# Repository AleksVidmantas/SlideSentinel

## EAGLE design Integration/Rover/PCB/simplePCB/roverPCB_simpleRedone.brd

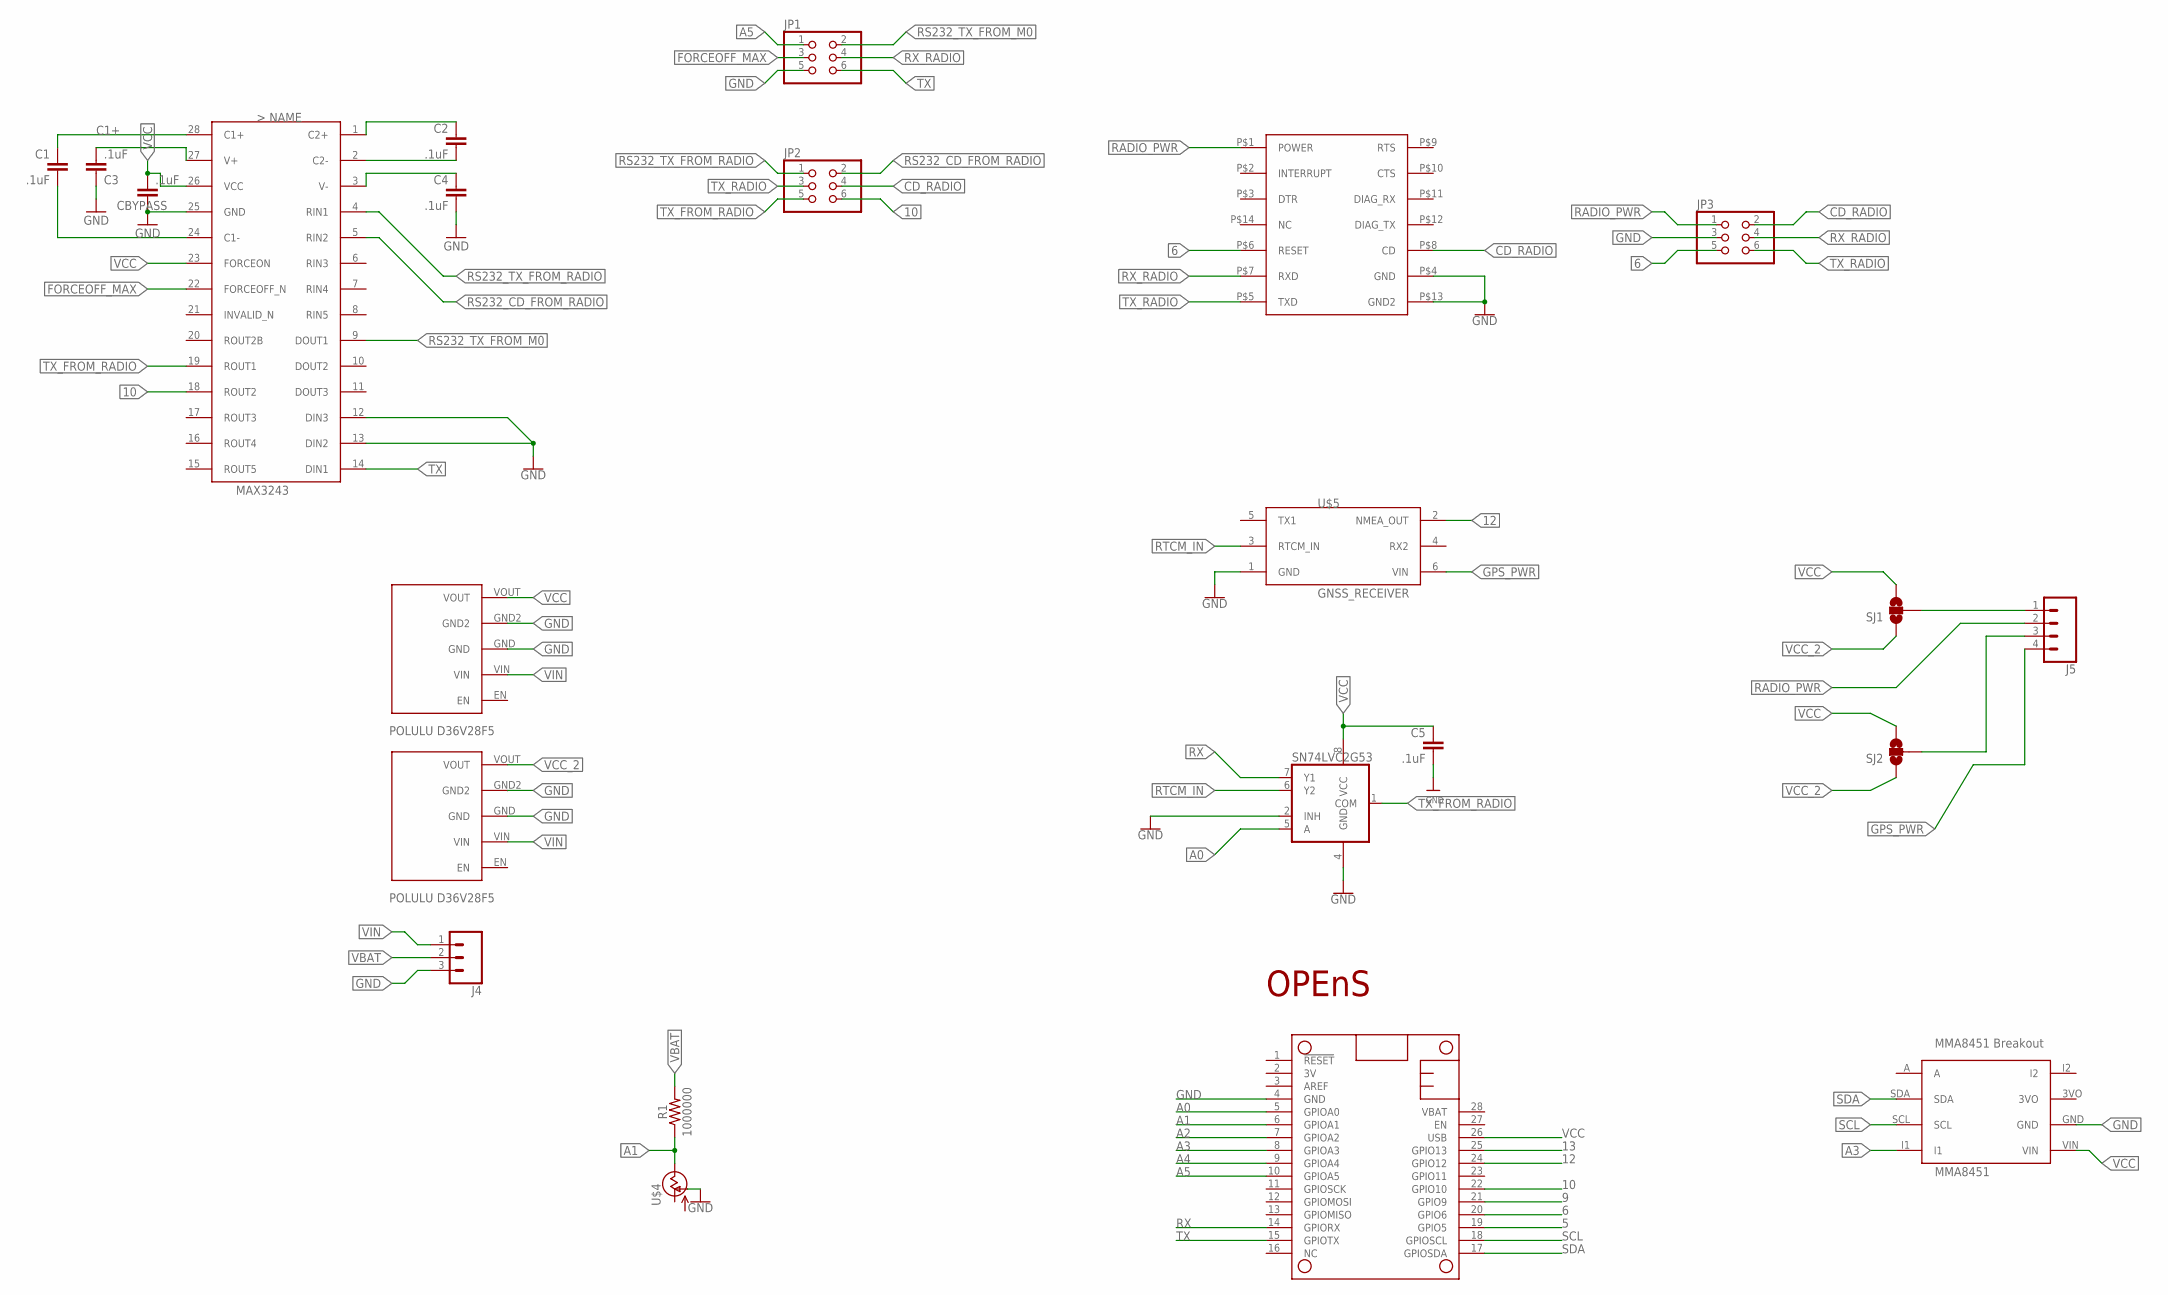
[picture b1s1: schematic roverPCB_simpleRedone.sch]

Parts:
C1, C2, C3, C4, C5: .1uF; C1206
CBYPASS: .1uF; C1206
J4: CONN_03SCREW; SCREWTERMINAL-3.5MM-3
J5: CONN_04SCREW; SCREWTERMINAL-3.5MM-4
JP1, JP2, JP3: PINHD-2X3; 2X03
MS1: FEATHERWING
R1: 1000000; 0603
SJ1, SJ2: SOLDERJUMPER_2WAY-OLDT; SJ_2
SN74LVC2G53: 741G53DCT; DCT_R-PDSO-G8
U$1: MAX3243; SSOP-28
U$2: OPENS-LOGO
U$3: Z9-T/Z9-CCOPY; Z9-T/Z9-C-COPY
U$4: CT6EP205; CT6
U$5: GNSS_RECEIVER; MA03-2
U$7, U$8: POLULU_D36V28FX
U$9: MMA8451

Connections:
5: MS1.19 (GPIO5)
6: JP3.5, MS1.20 (GPIO6), U$3.P$6 (RESET)
9: MS1.21 (GPIO9)
10: JP2.6, MS1.22 (GPIO10), U$1.18 (ROUT2)
12: MS1.24 (GPIO12), U$5.2 (NMEA_OUT)
13: MS1.25 (GPIO13)
A0: MS1.5 (GPIOA0), SN74LVC2G53.5 (A)
A1: MS1.6 (GPIOA1), R1.1, U$4.S (VSS)
A2: MS1.7 (GPIOA2)
A3: MS1.8 (GPIOA3), U$9.I1
A4: MS1.9 (GPIOA4)
A5: JP1.1, MS1.10 (GPIOA5)
C1+: C1.1, U$1.28 (C1+)
CD_RADIO: JP2.4, JP3.2, U$3.P$8 (CD)
FORCEOFF_MAX: JP1.3, U$1.22 (FORCEOFF_N)
GND: C3.1, C4.2, C5.2, CBYPASS.1, J4.3, JP1.5, JP3.3, MS1.4 (GND), SN74LVC2G53.2 (INH), SN74LVC2G53.4 (GND), U$1.12 (DIN3), U$1.13 (DIN2), U$1.25 (GND), U$3.P$4 (GND), U$3.P$13 (GND2), U$4.A (OUT), U$5.1 (GND), U$7.GND, U$7.GND2, U$8.GND, U$8.GND2, U$9.GND
GPS_PWR: J5.4, U$5.6 (VIN)
unnamed: C2.1, U$1.1 (C2+)
unnamed: C2.2, U$1.2 (C2-)
unnamed: J5.1, SJ1.2
unnamed: C4.1, U$1.3 (V-)
unnamed: C1.2, U$1.24 (C1-)
unnamed: J5.3, SJ2.2
unnamed: C3.2, U$1.27 (V+)
RADIO_PWR: J5.2, JP3.1, U$3.P$1 (POWER)
RS232_CD_FROM_RADIO: JP2.2, U$1.5 (RIN2)
RS232_TX_FROM_M0: JP1.2, U$1.9 (DOUT1)
RS232_TX_FROM_RADIO: JP2.1, U$1.4 (RIN1)
RTCM_IN: SN74LVC2G53.6 (Y2), U$5.3 (RTCM_IN)
RX: MS1.14 (GPIORX), SN74LVC2G53.7 (Y1)
RX_RADIO: JP1.4, JP3.4, U$3.P$7 (RXD)
SCL: MS1.18 (GPIOSCL), U$9.SCL
SDA: MS1.17 (GPIOSDA), U$9.SDA
TX: JP1.6, MS1.15 (GPIOTX), U$1.14 (DIN1)
TX_FROM_RADIO: JP2.5, SN74LVC2G53.1 (COM), U$1.19 (ROUT1)
TX_RADIO: JP2.3, JP3.6, U$3.P$5 (TXD)
VBAT: J4.2, R1.2
VCC: C5.1, CBYPASS.2, MS1.26 (USB), SJ1.3, SJ2.3, SN74LVC2G53.8 (VCC), U$1.23 (FORCEON), U$1.26 (VCC), U$7.VOUT, U$9.VIN
VCC_2: SJ1.1, SJ2.1, U$8.VOUT
VIN: J4.1, U$7.VIN, U$8.VIN

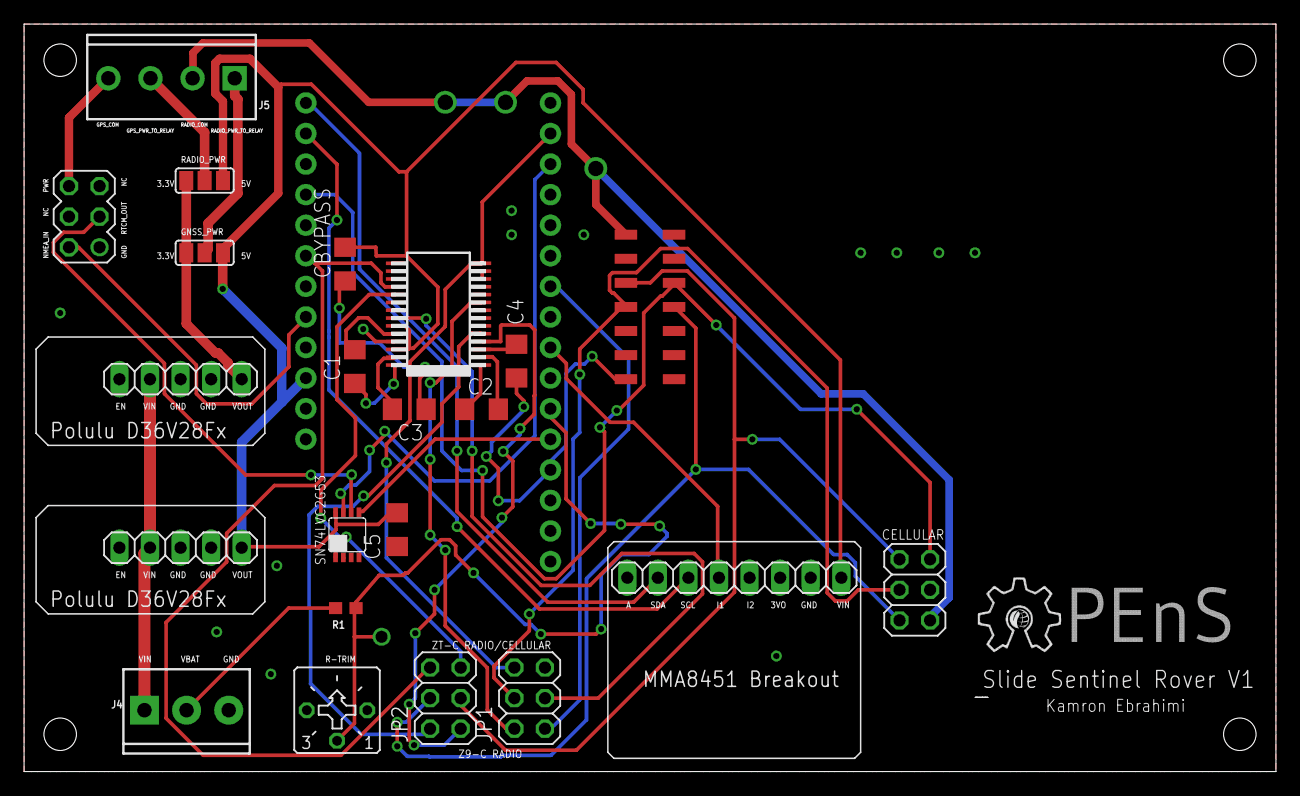
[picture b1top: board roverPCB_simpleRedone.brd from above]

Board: 2 copper layers, 104.0 x 62.1 mm, 24 parts (0 on the bottom side), 35 nets.

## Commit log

2019-08-19 Updated scripts to adjust index fields for NMEA format
2019-08-20 Diagram for testing module
2019-09-26 Updated pcb, network, rover.ino
2020-01-13 pushing AGU demo
2020-02-19 Finished RTCController
2020-02-20 moved content of m_initialize to init
2020-05-02 adding wiki photos for Sprint 2020
2020-05-02 added signal graphs for gnss receivers
2020-05-02 added photos for wiki
2020-05-02 added photo
2020-05-02 added photo of tallysman
2020-08-27 bug fixes

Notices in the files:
parts and their libraries:
SparkFun-Connectors: Licensing: Creative Commons ShareAlike 4.0 International - https://creativecommons.org/licenses/by-sa/4.0
microbuilder: This work is placed in the public domain, and may be freely used for commercial and non-commercial work with the following conditions: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
